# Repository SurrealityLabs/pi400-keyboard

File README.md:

# pi400-keyboard
A mechanical QWERTY keyboard for the Raspberry Pi 400

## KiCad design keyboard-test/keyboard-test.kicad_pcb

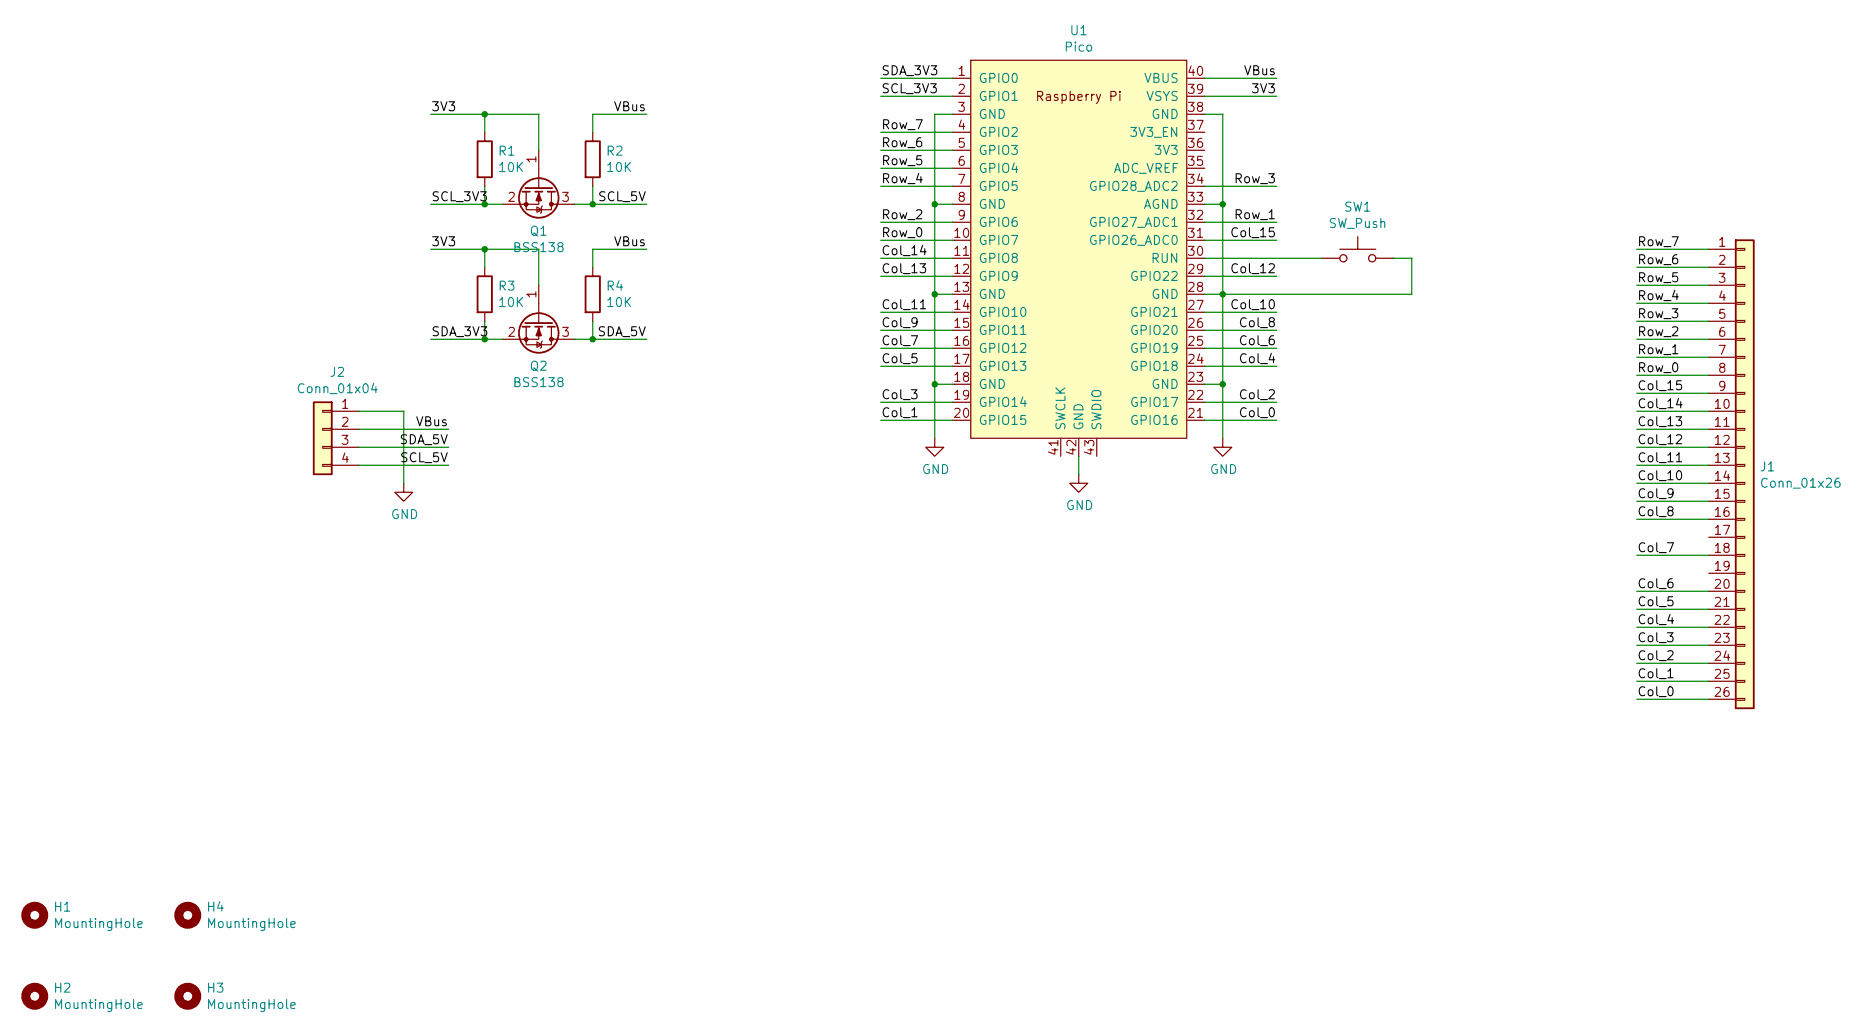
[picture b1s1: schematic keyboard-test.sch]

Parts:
H1, H2, H3, H4: MountingHole; MountingHole_3.2mm_M3_DIN965
J1: Conn_01x26; TE_2-84952-6_1x26-1MP_P1.0mm_Horizontal
J2: Conn_01x04; JST_PH_S4B-PH-SM4-TB_1x04-1MP_P2.00mm_Horizontal
Q1, Q2: BSS138; SOT-23
R1, R2, R3, R4: 10K; R_0603_1608Metric
SW1: SW_Push; SW_PUSH_6mm
U1: Pico; RPi_Pico_SMD_TH

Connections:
/3V3: Q1.1 (G), Q2.1 (G), R1.1, R3.1, U1.39 (VSYS)
/Col_0: J1.26, U1.21 (GPIO16)
/Col_1: J1.25, U1.20 (GPIO15)
/Col_2: J1.24, U1.22 (GPIO17)
/Col_3: J1.23, U1.19 (GPIO14)
/Col_4: J1.22, U1.24 (GPIO18)
/Col_5: J1.21, U1.17 (GPIO13)
/Col_6: J1.20, U1.25 (GPIO19)
/Col_7: J1.18, U1.16 (GPIO12)
/Col_8: J1.16, U1.26 (GPIO20)
/Col_9: J1.15, U1.15 (GPIO11)
/Col_10: J1.14, U1.27 (GPIO21)
/Col_11: J1.13, U1.14 (GPIO10)
/Col_12: J1.12, U1.29 (GPIO22)
/Col_13: J1.11, U1.12 (GPIO9)
/Col_14: J1.10, U1.11 (GPIO8)
/Col_15: J1.9, U1.31 (GPIO26_ADC0)
/Row_0: J1.8, U1.10 (GPIO7)
/Row_1: J1.7, U1.32 (GPIO27_ADC1)
/Row_2: J1.6, U1.9 (GPIO6)
/Row_3: J1.5, U1.34 (GPIO28_ADC2)
/Row_4: J1.4, U1.7 (GPIO5)
/Row_5: J1.3, U1.6 (GPIO4)
/Row_6: J1.2, U1.5 (GPIO3)
/Row_7: J1.1, U1.4 (GPIO2)
/SCL_3V3: Q1.2 (S), R1.2, U1.2 (GPIO1)
/SCL_5V: J2.4, Q1.3 (D), R2.2
/SDA_3V3: Q2.2 (S), R3.2, U1.1 (GPIO0)
/SDA_5V: J2.3, Q2.3 (D), R4.2
/VBus: J2.2, R2.1, R4.1, U1.40 (VBUS)
GND: J2.1, SW1.2, U1.3 (GND), U1.8 (GND), U1.13 (GND), U1.18 (GND), U1.23 (GND), U1.28 (GND), U1.33 (AGND), U1.38 (GND), U1.42 (GND)
unnamed: SW1.1, U1.30 (RUN)

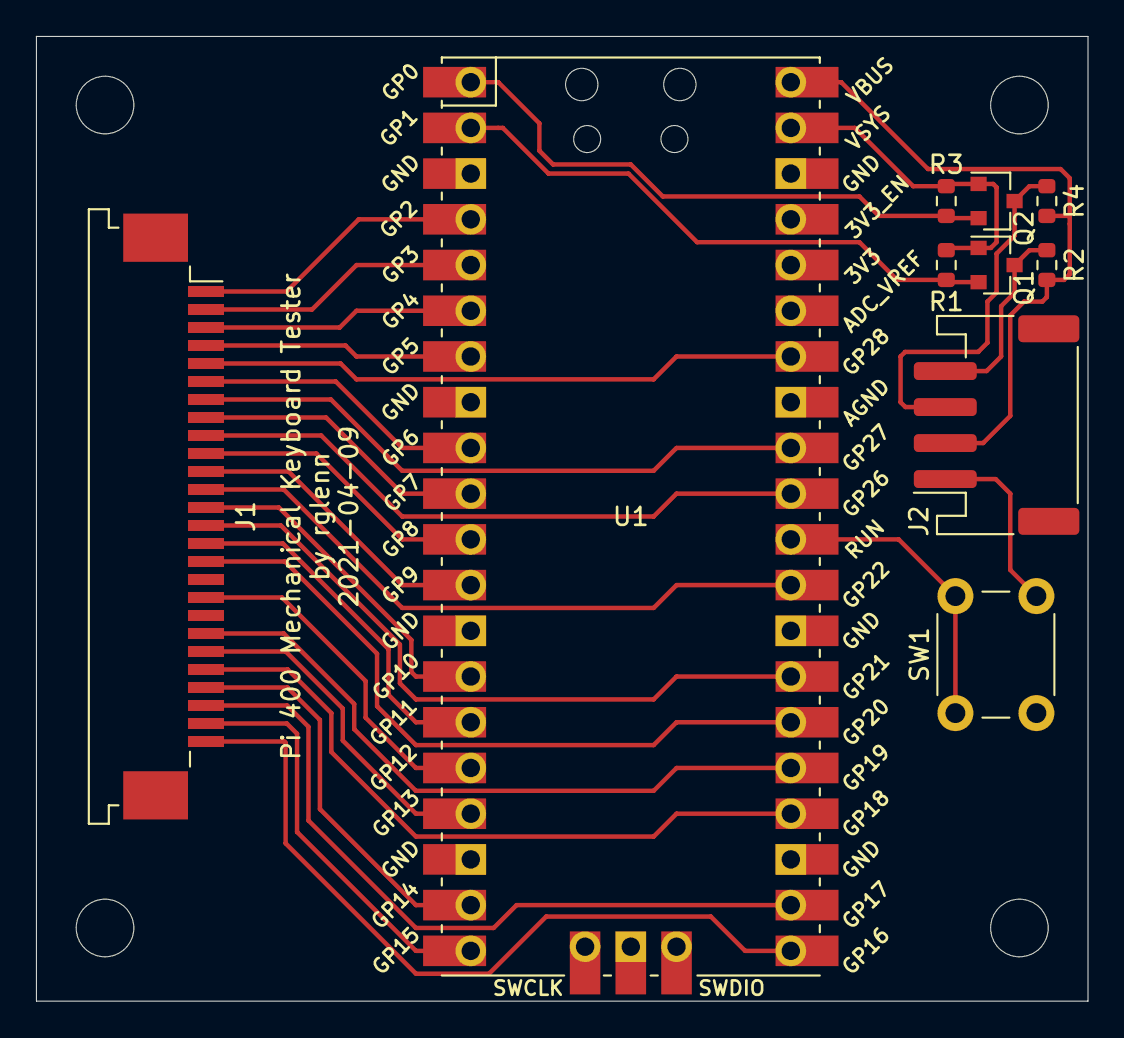
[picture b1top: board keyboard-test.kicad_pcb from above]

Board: 2 copper layers, 58.4 x 53.6 mm, 14 parts (0 on the bottom side), 32 nets.

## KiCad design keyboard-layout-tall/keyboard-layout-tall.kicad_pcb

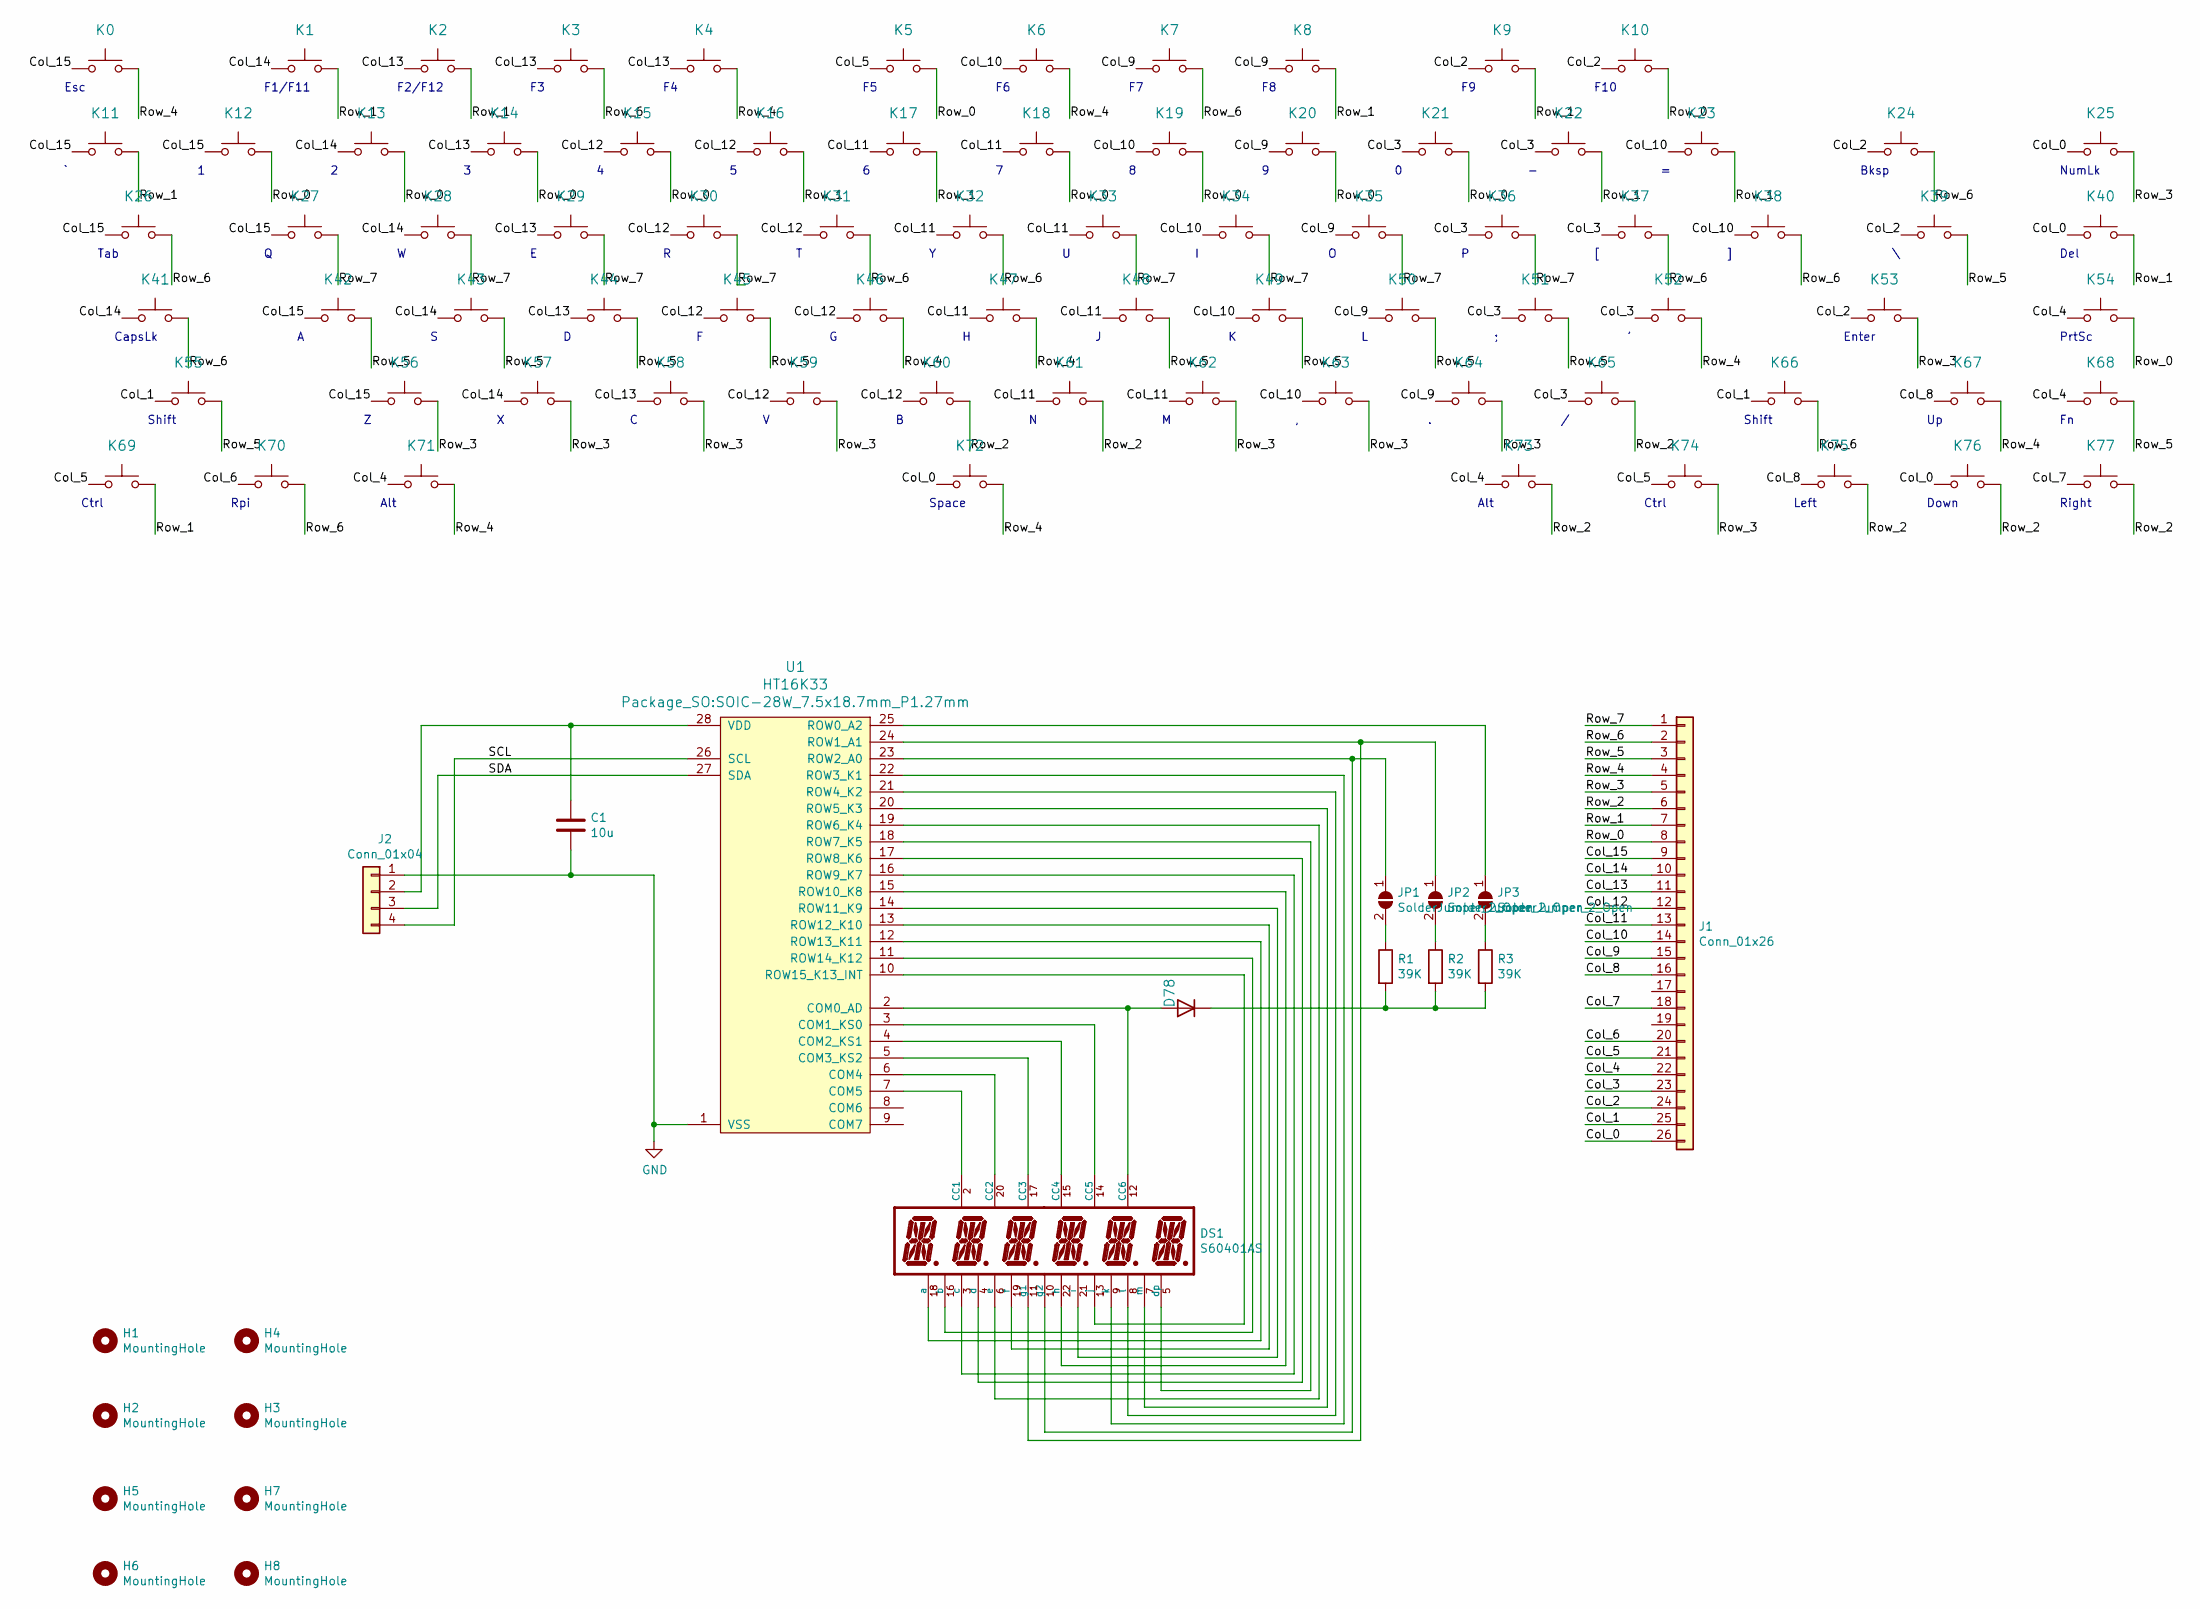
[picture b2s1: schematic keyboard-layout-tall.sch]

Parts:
C1: 10u; C_0805_2012Metric; LCSC C15850
D78: D; D_SOD-123F; LCSC C64898
DS1: S60401AS
H1, H2, H3, H4, H5, H6, H7, H8: MountingHole; MountingHole_3.2mm_M3_DIN965
J1: Conn_01x26; TE_2-84952-6_1x26-1MP_P1.0mm_Horizontal
J2: Conn_01x04; JST_PH_S4B-PH-SM4-TB_1x04-1MP_P2.00mm_Horizontal
JP1, JP2, JP3: SolderJumper_2_Open; SolderJumper-2_P1.3mm_Open_RoundedPad1.0x1.5mm
K0, K1, K2, K3, K4, K5, K6, K7, K8, K9, K10, K11, K12, K13, K14, K15, K16, K17, K18, K19, K20, K21, K22, K23, K25, K27, K28, K29, K30, K31, K32, K33, K34, K35, K36, K37, K38, K40, K42, K43, K44, K45, K46, K47, K48, K49, K50, K51, K52, K54, K56, K57, K58, K59, K60, K61, K62, K63, K64, K65, K67, K68, K70, K75, K76, K77: KEYSW; SW_Cherry_MX_1.00u_PCB
K24: KEYSW; SW_Cherry_MX_2.00u_PCB
K26, K39: KEYSW; SW_Cherry_MX_1.50u_PCB
K41, K66: KEYSW; SW_Cherry_MX_1.75u_PCB
K53, K55: KEYSW; SW_Cherry_MX_2.25u_PCB
K69, K71, K73, K74: KEYSW; SW_Cherry_MX_1.25u_PCB
K72: KEYSW; SW_Cherry_MX_7u_PCB
R1, R2, R3: 39K; R_0603_1608Metric; LCSC C23153
U1: HT16K33; SOIC-28W_7.5x18.7mm_P1.27mm

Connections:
/Col_0: J1.26, K25.1, K40.1, K72.1, K76.1
/Col_1: J1.25, K55.1, K66.1
/Col_2: J1.24, K9.1, K10.1, K24.1, K39.1, K53.1
/Col_3: J1.23, K21.1, K22.1, K36.1, K37.1, K51.1, K52.1, K65.1
/Col_4: J1.22, K54.1, K68.1, K71.1, K73.1
/Col_5: J1.21, K5.1, K69.1, K74.1
/Col_6: J1.20, K70.1
/Col_7: J1.18, K77.1
/Col_8: J1.16, K67.1, K75.1
/Col_9: J1.15, K7.1, K8.1, K20.1, K35.1, K50.1, K64.1
/Col_10: J1.14, K6.1, K19.1, K23.1, K34.1, K38.1, K49.1, K63.1
/Col_11: J1.13, K17.1, K18.1, K32.1, K33.1, K47.1, K48.1, K61.1, K62.1
/Col_12: J1.12, K15.1, K16.1, K30.1, K31.1, K45.1, K46.1, K59.1, K60.1
/Col_13: J1.11, K2.1, K3.1, K4.1, K14.1, K29.1, K44.1, K58.1
/Col_14: J1.10, K1.1, K13.1, K28.1, K41.1, K43.1, K57.1
/Col_15: J1.9, K0.1, K11.1, K12.1, K26.1, K27.1, K42.1, K56.1
/Row_0: J1.8, K5.2, K10.2, K12.2, K13.2, K14.2, K15.2, K18.2, K19.2, K20.2, K21.2, K54.2
/Row_1: J1.7, K1.2, K2.2, K8.2, K9.2, K11.2, K16.2, K17.2, K22.2, K23.2, K40.2, K69.2
/Row_2: J1.6, K60.2, K61.2, K65.2, K73.2, K75.2, K76.2, K77.2
/Row_3: J1.5, K25.2, K53.2, K56.2, K57.2, K58.2, K59.2, K62.2, K63.2, K64.2, K74.2
/Row_4: J1.4, K0.2, K4.2, K6.2, K46.2, K47.2, K52.2, K67.2, K71.2, K72.2
/Row_5: J1.3, K39.2, K42.2, K43.2, K44.2, K45.2, K48.2, K49.2, K50.2, K51.2, K55.2, K68.2
/Row_6: J1.2, K3.2, K7.2, K24.2, K26.2, K31.2, K32.2, K37.2, K38.2, K41.2, K66.2, K70.2
/Row_7: J1.1, K27.2, K28.2, K29.2, K30.2, K33.2, K34.2, K35.2, K36.2
/SCL: J2.4, U1.26 (SCL)
/SDA: J2.3, U1.27 (SDA)
GND: C1.2, J2.1, U1.1 (VSS)
unnamed: C1.1, J2.2, U1.28 (VDD)
unnamed: D78.1 (K), R1.2, R2.2, R3.2
unnamed: D78.2 (A), DS1.12 (CC6), U1.2 (COM0_AD)
unnamed: DS1.2 (CC1), U1.7 (COM5)
unnamed: DS1.3 (c), U1.16 (ROW9_K7)
unnamed: DS1.4 (d), U1.17 (ROW8_K6)
unnamed: DS1.5 (dp), U1.18 (ROW7_K5)
unnamed: DS1.6 (e), U1.19 (ROW6_K4)
unnamed: DS1.7 (m), U1.20 (ROW5_K3)
unnamed: DS1.8 (l), U1.21 (ROW4_K2)
unnamed: DS1.9 (k), U1.22 (ROW3_K1)
unnamed: DS1.10 (g2), JP1.1 (A), U1.23 (ROW2_A0)
unnamed: DS1.11 (g1), JP2.1 (A), U1.24 (ROW1_A1)
unnamed: DS1.13 (j), U1.10 (ROW15_K13_INT)
unnamed: DS1.14 (CC5), U1.3 (COM1_KS0)
unnamed: DS1.15 (CC4), U1.4 (COM2_KS1)
unnamed: DS1.16 (b), U1.11 (ROW14_K12)
unnamed: DS1.17 (CC3), U1.5 (COM3_KS2)
unnamed: DS1.18 (a), U1.12 (ROW13_K11)
unnamed: DS1.19 (f), U1.13 (ROW12_K10)
unnamed: DS1.20 (CC2), U1.6 (COM4)
unnamed: DS1.21 (i), U1.14 (ROW11_K9)
unnamed: DS1.22 (h), U1.15 (ROW10_K8)
unnamed: JP1.2 (B), R1.1
unnamed: JP2.2 (B), R2.1
unnamed: JP3.1 (A), U1.25 (ROW0_A2)
unnamed: JP3.2 (B), R3.1

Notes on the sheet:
Esc
F1/F11
F2/F12
F10
Bksp
NumLk
Tab
Del
CapsLk
Enter
PrtSc
Shift
Ctrl
Rpi
Alt
Space
Left
Down
Right

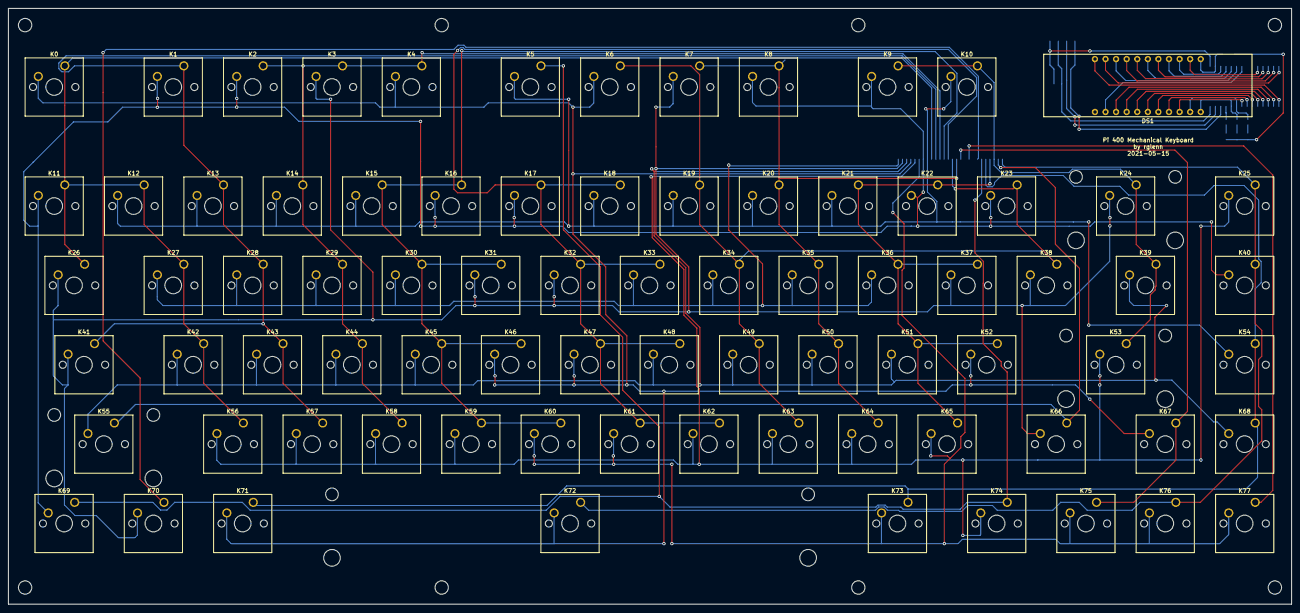
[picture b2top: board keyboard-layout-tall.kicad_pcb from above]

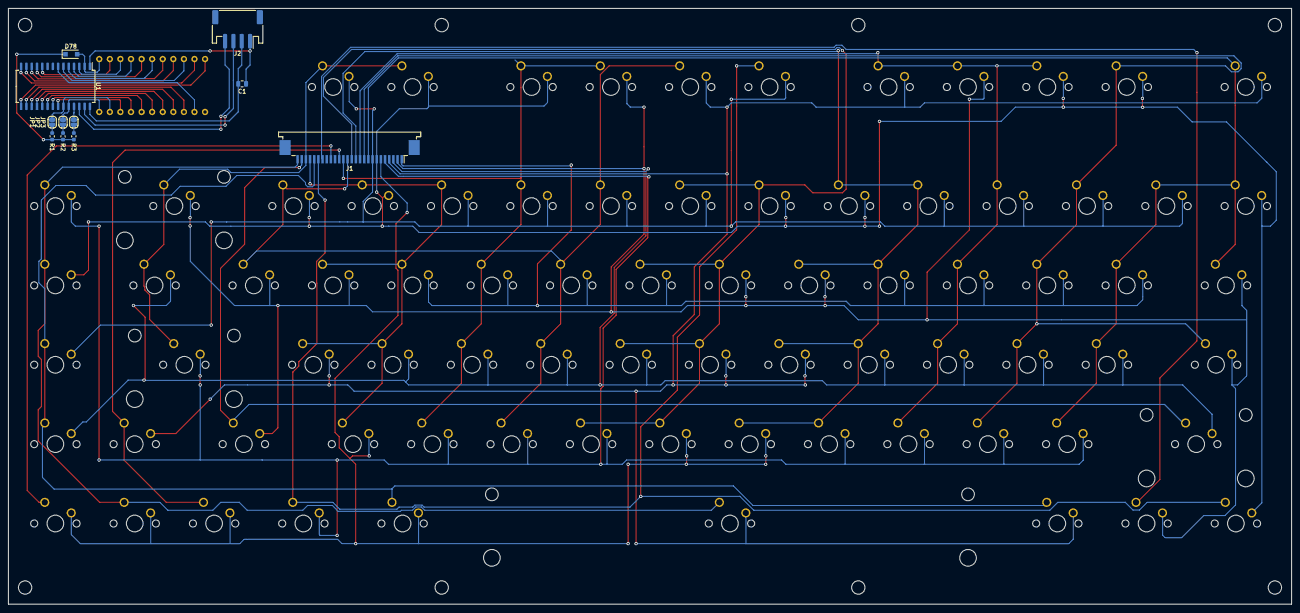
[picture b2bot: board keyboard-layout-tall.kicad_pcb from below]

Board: 2 copper layers, 308.0 x 143.0 mm, 98 parts (11 on the bottom side), 54 nets.

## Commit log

2021-05-12 Adding first rev of keyboard. Diodes need to be removed and replaced with shorts - the Pi 400's keyboard controller doesn't register any keypresses when you have diodes in the matrix. Even Schottky d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
2021-05-15 Updated board to remove diodes. 2021-05-15 version should work right out of the box.
2025-02-03 Adding keyboard tester
